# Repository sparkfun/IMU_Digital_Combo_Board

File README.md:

IMU Digital Combo Board-6 Degrees of Freedom-ITG3200/ADXL345
====================================================================
[
*IMU Digital Combo (SEN-10121)*](https://www.sparkfun.com/products/10121)

A simple breakout for the ADXL345 accelerometer and the ITG-3200 MEMS gyro. This board communicates over I2C. 

Repository Contents
-------------------
* **/Hardware** - All Eagle design files (.brd, .sch)
* **/Libraries** - All Arduino libraries and board examples
* **/Production** - Test bed files and production panel files

License Information
-------------------
The hardware is released under [Creative Commons ShareAlike 4.0 International](https://creativecommons.org/licenses/by-sa/4.0/).
The code is beerware; if you see me (or any other SparkFun employee) at the local, and you've found our code helpful, please buy us a round!

Distributed as-is; no warranty is given.

The original code library can be found [here](https://github.com/a1ronzo/6DOF-Digital).

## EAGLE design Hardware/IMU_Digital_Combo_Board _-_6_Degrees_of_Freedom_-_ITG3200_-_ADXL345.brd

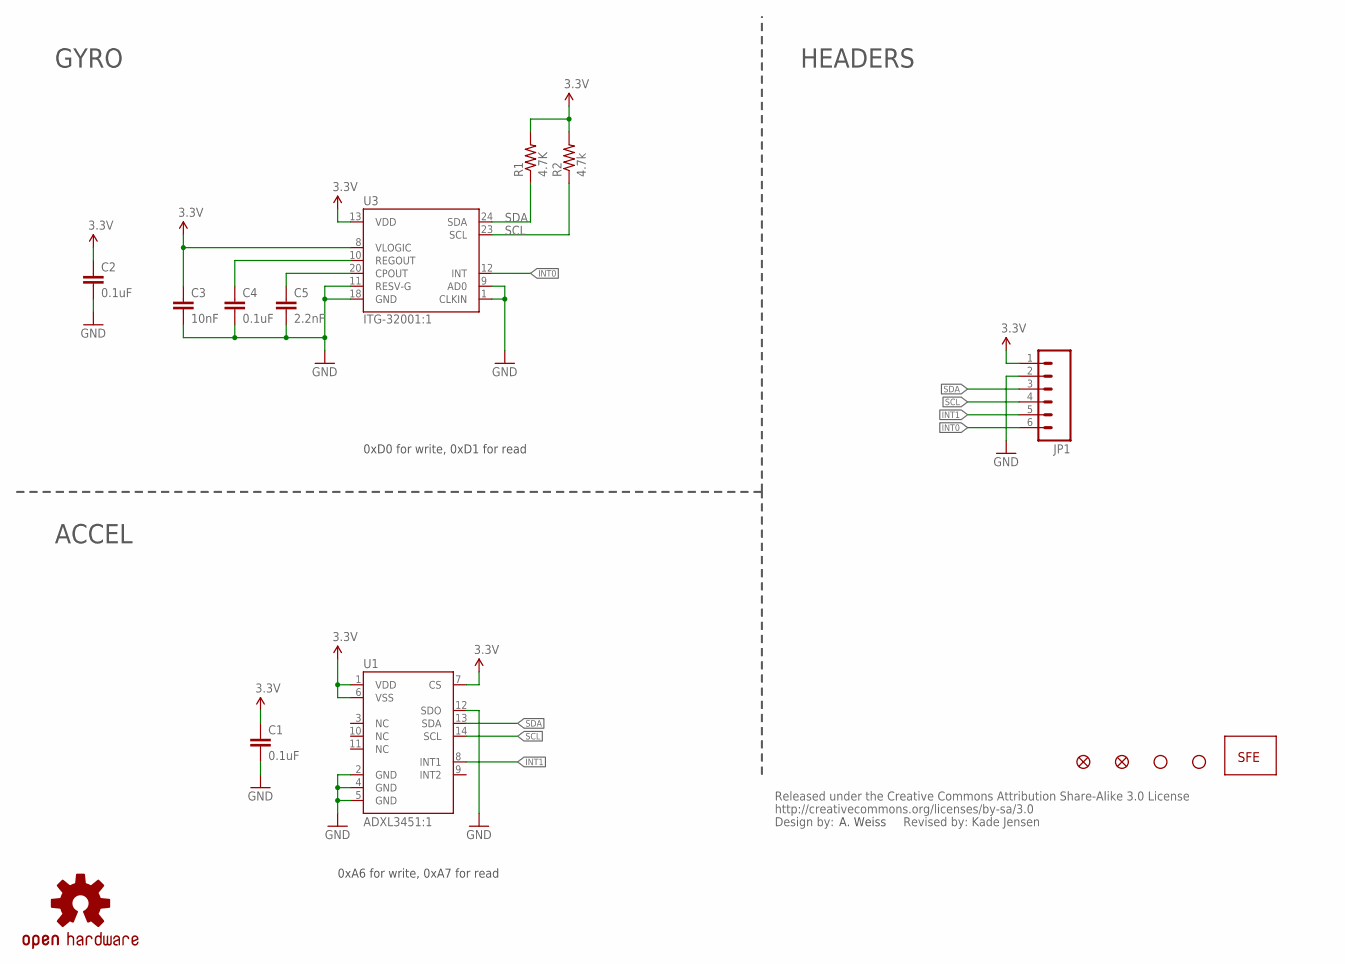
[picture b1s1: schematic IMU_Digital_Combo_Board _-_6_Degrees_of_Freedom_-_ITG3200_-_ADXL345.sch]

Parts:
C1, C2, C4: 0.1uF; 0603-CAP
C3: 10nF; 0603-CAP
C5: 2.2nF; 0603-CAP
JP1: M06SIP; 1X06
JP2, JP5: STAND-OFF
JP3: LOGO-SFESK; SFE-LOGO-FLAME
JP4, JP6: FIDUCIAL1X2; FIDUCIAL-1X2
R1: 4.7K; 0603-RES
R2: 4.7k; 0603-RES
U1: ADXL3451:1; LGA14
U3: ITG-32001:1; QFN-24_ITG3200_1:1
U$1: CREATIVE_COMMONS
U$2: OSHW-LOGOS; OSHW-LOGO-S

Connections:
3.3V: C1.1, C2.1, C3.1, JP1.1, R1.2, R2.2, U1.1 (VDD), U1.6 (VSS), U1.7 (CS), U3.8 (VLOGIC), U3.13 (VDD)
GND: C1.2, C2.2, C3.2, C4.2, C5.2, JP1.2, U1.2 (GND), U1.4 (GND), U1.5 (GND), U1.12 (SDO), U3.1 (CLKIN), U3.9 (AD0), U3.11 (RESV-G), U3.18 (GND)
INT0: JP1.6, U3.12 (INT)
INT1: JP1.5, U1.8 (INT1)
unnamed: C5.1, U3.20 (CPOUT)
unnamed: C4.1, U3.10 (REGOUT)
SCL: JP1.4, R2.1, U1.14 (SCL), U3.23 (SCL)
SDA: JP1.3, R1.1, U1.13 (SDA), U3.24 (SDA)

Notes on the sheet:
A. Weiss
GYRO
ACCEL
HEADERS
0xD0 for write, 0xD1 for read
0xA6 for write, 0xA7 for read
Revised by: Kade Jensen

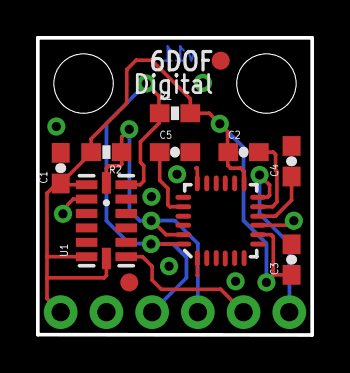
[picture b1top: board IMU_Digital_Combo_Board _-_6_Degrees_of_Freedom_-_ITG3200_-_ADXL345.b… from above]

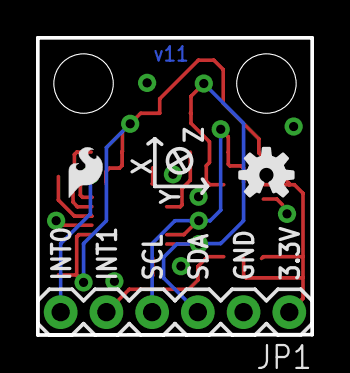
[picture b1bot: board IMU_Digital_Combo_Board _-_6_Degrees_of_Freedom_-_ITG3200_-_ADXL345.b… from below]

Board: 2 copper layers, 15.2 x 16.5 mm, 17 parts (3 on the bottom side), 8 nets.

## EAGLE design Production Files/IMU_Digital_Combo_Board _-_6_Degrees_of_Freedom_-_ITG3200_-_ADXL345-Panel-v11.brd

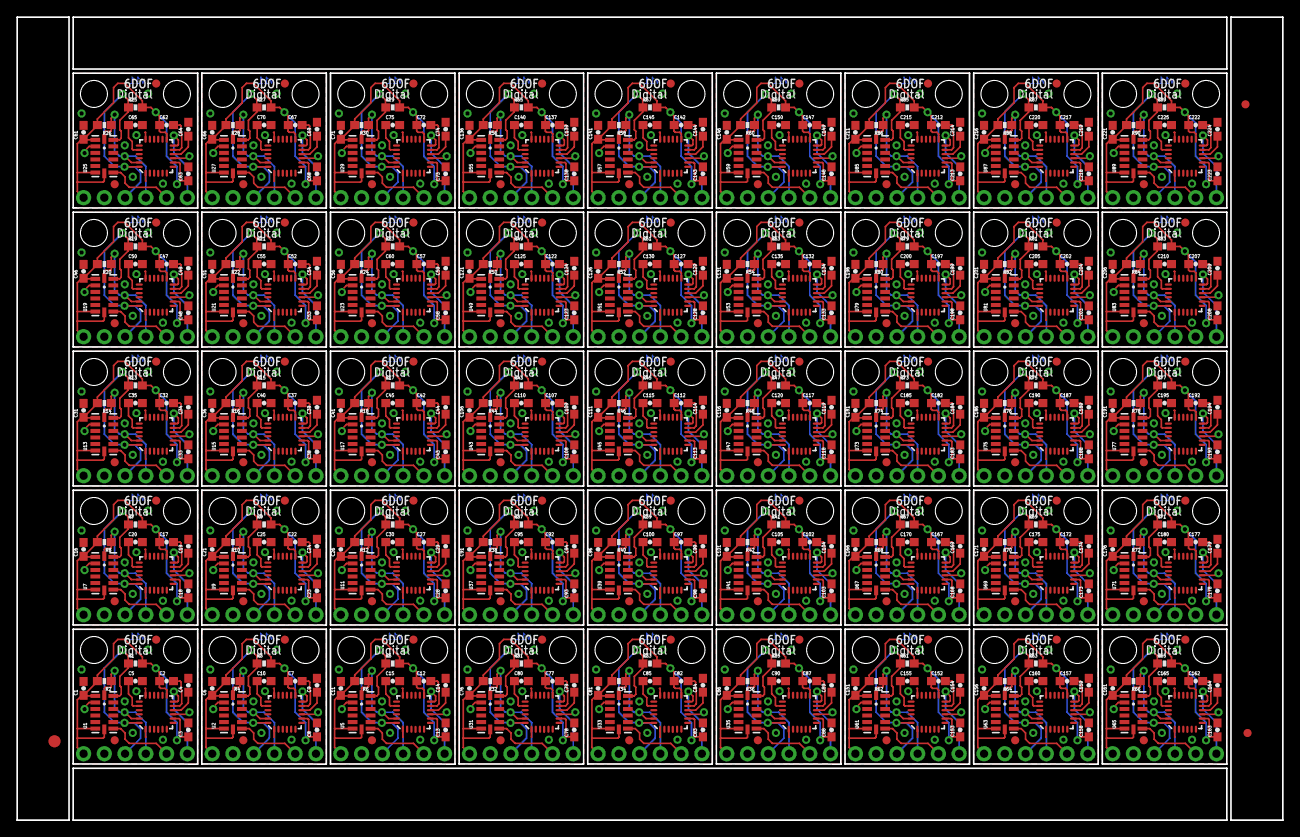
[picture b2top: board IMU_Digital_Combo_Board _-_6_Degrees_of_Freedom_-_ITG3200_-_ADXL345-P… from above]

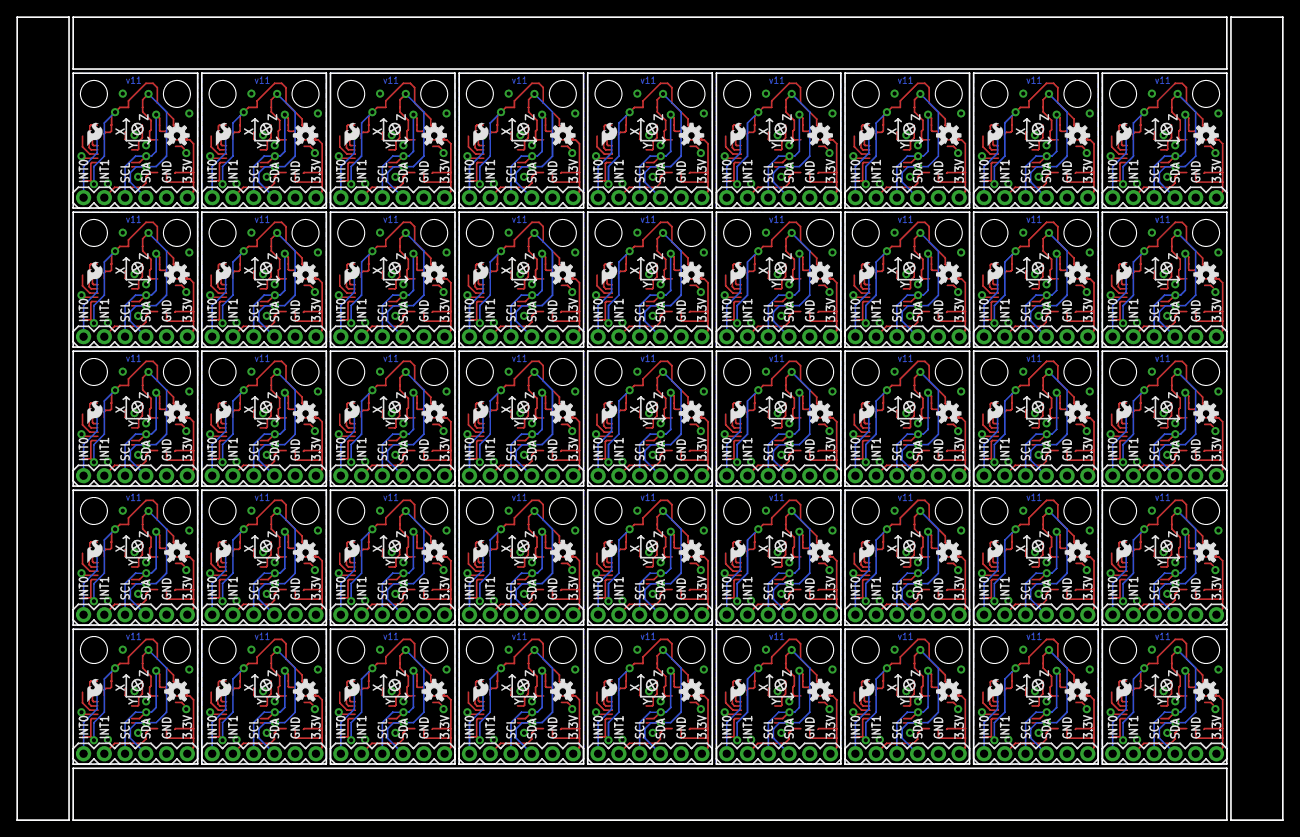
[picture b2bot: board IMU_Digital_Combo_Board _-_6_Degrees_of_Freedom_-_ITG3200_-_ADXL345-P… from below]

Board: 2 copper layers, 154.9 x 98.3 mm, 723 parts (135 on the bottom side), 360 nets.

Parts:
C1, C2, C4, C6, C7, C9, C11, C12, C14, C16, C17, C19, C21, C22, C24, C26, C27, C29, C31, C32, C34, C36, C37, C39, C41, C42, C44, C46, C47, C49, C51, C52, C54, C56, C57, C59, C61, C62, C64, C66, C67, C69, C71, C72, C74, C76, C77, C79, C81, C82, C84, C86, C87, C89, C91, C92, C94, C96, C97, C99, C101, C102, C104, C106, C107, C109, C111, C112, C114, C116, C117, C119, C121, C122, C124, C126, C127, C129, C131, C132, C134, C136, C137, C139, C141, C142, C144, C146, C147, C149, C151, C152, C154, C156, C157, C159, C161, C162, C164, C166, C167, C169, C171, C172, C174, C176, C177, C179, C181, C182, C184, C186, C187, C189, C191, C192, C194, C196, C197, C199, C201, C202, C204, C206, C207, C209, C211, C212, C214, C216, C217, C219, C221, C222, C224: 0.1uF; 0603-CAP
C3, C8, C13, C18, C23, C28, C33, C38, C43, C48, C53, C58, C63, C68, C73, C78, C83, C88, C93, C98, C103, C108, C113, C118, C123, C128, C133, C138, C143, C148, C153, C158, C163, C168, C173, C178, C183, C188, C193, C198, C203, C208, C213, C218, C223: 10nF; 0603-CAP
C5, C10, C15, C20, C25, C30, C35, C40, C45, C50, C55, C60, C65, C70, C75, C80, C85, C90, C95, C100, C105, C110, C115, C120, C125, C130, C135, C140, C145, C150, C155, C160, C165, C170, C175, C180, C185, C190, C195, C200, C205, C210, C215, C220, C225: 2.2nF; 0603-CAP
E$1: FIDUCIAL-1.5X3
E$4, E$6: FIDUCIAL-1X2
JP1, JP8, JP14, JP20, JP26, JP32, JP38, JP44, JP50, JP56, JP62, JP68, JP74, JP80, JP86, JP92, JP98, JP104, JP110, JP116, JP122, JP128, JP134, JP140, JP146, JP152, JP158, JP164, JP170, JP176, JP182, JP188, JP194, JP200, JP206, JP212, JP218, JP224, JP230, JP236, JP242, JP248, JP254, JP260, JP266: 1X06
JP2, JP5, JP9, JP10, JP15, JP16, JP21, JP22, JP27, JP28, JP33, JP34, JP39, JP40, JP45, JP46, JP51, JP52, JP57, JP58, JP63, JP64, JP69, JP70, JP75, JP76, JP81, JP82, JP87, JP88, JP93, JP94, JP99, JP100, JP105, JP106, JP111, JP112, JP117, JP118, JP123, JP124, JP129, JP130, JP135, JP136, JP141, JP142, JP147, JP148, JP153, JP154, JP159, JP160, JP165, JP166, JP171, JP172, JP177, JP178, JP183, JP184, JP189, JP190, JP195, JP196, JP201, JP202, JP207, JP208, JP213, JP214, JP219, JP220, JP225, JP226, JP231, JP232, JP237, JP238, JP243, JP244, JP249, JP250, JP255, JP256, JP261, JP262, JP267, JP268: STAND-OFF
JP3, JP7, JP13, JP19, JP25, JP31, JP37, JP43, JP49, JP55, JP61, JP67, JP73, JP79, JP85, JP91, JP97, JP103, JP109, JP115, JP121, JP127, JP133, JP139, JP145, JP151, JP157, JP163, JP169, JP175, JP181, JP187, JP193, JP199, JP205, JP211, JP217, JP223, JP229, JP235, JP241, JP247, JP253, JP259, JP265: LOGO-SFESK; SFE-LOGO-FLAME
JP4, JP6, JP11, JP12, JP17, JP18, JP23, JP24, JP29, JP30, JP35, JP36, JP41, JP42, JP47, JP48, JP53, JP54, JP59, JP60, JP65, JP66, JP71, JP72, JP77, JP78, JP83, JP84, JP89, JP90, JP95, JP96, JP101, JP102, JP107, JP108, JP113, JP114, JP119, JP120, JP125, JP126, JP131, JP132, JP137, JP138, JP143, JP144, JP149, JP150, JP155, JP156, JP161, JP162, JP167, JP168, JP173, JP174, JP179, JP180, JP185, JP186, JP191, JP192, JP197, JP198, JP203, JP204, JP209, JP210, JP215, JP216, JP221, JP222, JP227, JP228, JP233, JP234, JP239, JP240, JP245, JP246, JP251, JP252, JP257, JP258, JP263, JP264, JP269, JP270: FIDUCIAL1X2; FIDUCIAL-1X2
R1, R3, R5, R7, R9, R11, R13, R15, R17, R19, R21, R23, R25, R27, R29, R31, R33, R35, R37, R39, R41, R43, R45, R47, R49, R51, R53, R55, R57, R59, R61, R63, R65, R67, R69, R71, R73, R75, R77, R79, R81, R83, R85, R87, R89: 4.7K; 0603-RES
R2, R4, R6, R8, R10, R12, R14, R16, R18, R20, R22, R24, R26, R28, R30, R32, R34, R36, R38, R40, R42, R44, R46, R48, R50, R52, R54, R56, R58, R60, R62, R64, R66, R68, R70, R72, R74, R76, R78, R80, R82, R84, R86, R88, R90: 4.7k; 0603-RES
U1, U2, U5, U7, U9, U11, U13, U15, U17, U19, U21, U23, U25, U27, U29, U31, U33, U35, U37, U39, U41, U43, U45, U47, U49, U51, U53, U55, U57, U59, U61, U63, U65, U67, U69, U71, U73, U75, U77, U79, U81, U83, U85, U87, U89: ADXL3451:1; LGA14
U3, U4, U6, U8, U10, U12, U14, U16, U18, U20, U22, U24, U26, U28, U30, U32, U34, U36, U38, U40, U42, U44, U46, U48, U50, U52, U54, U56, U58, U60, U62, U64, U66, U68, U70, U72, U74, U76, U78, U80, U82, U84, U86, U88, U90: ITG-32001:1; QFN-24_ITG3200_1:1
U$1, U$2, U$3, U$4, U$5, U$6, U$7, U$8, U$9, U$10, U$11, U$12, U$13, U$14, U$15, U$16, U$17, U$18, U$19, U$20, U$21, U$22, U$23, U$24, U$25, U$26, U$27, U$28, U$29, U$30, U$31, U$32, U$33, U$34, U$35, U$36, U$37, U$38, U$39, U$40, U$41, U$42, U$43, U$44, U$45: OSHW-LOGOS; OSHW-LOGO-S

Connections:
3.3V: C1.1, C2.1, C3.1, JP1.1, R1.2, R2.2, U1.1, U1.6, U1.7, U3.8, U3.13
3.3V1: C6.1, C7.1, C8.1, JP8.1, R3.2, R4.2, U2.1, U2.6, U2.7, U4.8, U4.13
3.3V2: C11.1, C12.1, C13.1, JP14.1, R5.2, R6.2, U5.1, U5.6, U5.7, U6.8, U6.13
3.3V3: C16.1, C17.1, C18.1, JP20.1, R7.2, R8.2, U7.1, U7.6, U7.7, U8.8, U8.13
3.3V4: C21.1, C22.1, C23.1, JP26.1, R9.2, R10.2, U9.1, U9.6, U9.7, U10.8, U10.13
3.3V5: C26.1, C27.1, C28.1, JP32.1, R11.2, R12.2, U11.1, U11.6, U11.7, U12.8, U12.13
3.3V6: C31.1, C32.1, C33.1, JP38.1, R13.2, R14.2, U13.1, U13.6, U13.7, U14.8, U14.13
3.3V7: C36.1, C37.1, C38.1, JP44.1, R15.2, R16.2, U15.1, U15.6, U15.7, U16.8, U16.13
3.3V8: C41.1, C42.1, C43.1, JP50.1, R17.2, R18.2, U17.1, U17.6, U17.7, U18.8, U18.13
3.3V9: C46.1, C47.1, C48.1, JP56.1, R19.2, R20.2, U19.1, U19.6, U19.7, U20.8, U20.13
3.3V10: C51.1, C52.1, C53.1, JP62.1, R21.2, R22.2, U21.1, U21.6, U21.7, U22.8, U22.13
3.3V11: C56.1, C57.1, C58.1, JP68.1, R23.2, R24.2, U23.1, U23.6, U23.7, U24.8, U24.13
3.3V12: C61.1, C62.1, C63.1, JP74.1, R25.2, R26.2, U25.1, U25.6, U25.7, U26.8, U26.13
3.3V13: C66.1, C67.1, C68.1, JP80.1, R27.2, R28.2, U27.1, U27.6, U27.7, U28.8, U28.13
3.3V14: C71.1, C72.1, C73.1, JP86.1, R29.2, R30.2, U29.1, U29.6, U29.7, U30.8, U30.13
3.3V15: C76.1, C77.1, C78.1, JP92.1, R31.2, R32.2, U31.1, U31.6, U31.7, U32.8, U32.13
3.3V16: C81.1, C82.1, C83.1, JP98.1, R33.2, R34.2, U33.1, U33.6, U33.7, U34.8, U34.13
3.3V17: C86.1, C87.1, C88.1, JP104.1, R35.2, R36.2, U35.1, U35.6, U35.7, U36.8, U36.13
3.3V18: C91.1, C92.1, C93.1, JP110.1, R37.2, R38.2, U37.1, U37.6, U37.7, U38.8, U38.13
3.3V19: C96.1, C97.1, C98.1, JP116.1, R39.2, R40.2, U39.1, U39.6, U39.7, U40.8, U40.13
3.3V20: C101.1, C102.1, C103.1, JP122.1, R41.2, R42.2, U41.1, U41.6, U41.7, U42.8, U42.13
3.3V21: C106.1, C107.1, C108.1, JP128.1, R43.2, R44.2, U43.1, U43.6, U43.7, U44.8, U44.13
3.3V22: C111.1, C112.1, C113.1, JP134.1, R45.2, R46.2, U45.1, U45.6, U45.7, U46.8, U46.13
3.3V23: C116.1, C117.1, C118.1, JP140.1, R47.2, R48.2, U47.1, U47.6, U47.7, U48.8, U48.13
3.3V24: C121.1, C122.1, C123.1, JP146.1, R49.2, R50.2, U49.1, U49.6, U49.7, U50.8, U50.13
3.3V25: C126.1, C127.1, C128.1, JP152.1, R51.2, R52.2, U51.1, U51.6, U51.7, U52.8, U52.13
3.3V26: C131.1, C132.1, C133.1, JP158.1, R53.2, R54.2, U53.1, U53.6, U53.7, U54.8, U54.13
3.3V27: C136.1, C137.1, C138.1, JP164.1, R55.2, R56.2, U55.1, U55.6, U55.7, U56.8, U56.13
3.3V28: C141.1, C142.1, C143.1, JP170.1, R57.2, R58.2, U57.1, U57.6, U57.7, U58.8, U58.13
3.3V29: C146.1, C147.1, C148.1, JP176.1, R59.2, R60.2, U59.1, U59.6, U59.7, U60.8, U60.13
3.3V30: C151.1, C152.1, C153.1, JP182.1, R61.2, R62.2, U61.1, U61.6, U61.7, U62.8, U62.13
3.3V31: C156.1, C157.1, C158.1, JP188.1, R63.2, R64.2, U63.1, U63.6, U63.7, U64.8, U64.13
3.3V32: C161.1, C162.1, C163.1, JP194.1, R65.2, R66.2, U65.1, U65.6, U65.7, U66.8, U66.13
3.3V33: C166.1, C167.1, C168.1, JP200.1, R67.2, R68.2, U67.1, U67.6, U67.7, U68.8, U68.13
3.3V34: C171.1, C172.1, C173.1, JP206.1, R69.2, R70.2, U69.1, U69.6, U69.7, U70.8, U70.13
3.3V35: C176.1, C177.1, C178.1, JP212.1, R71.2, R72.2, U71.1, U71.6, U71.7, U72.8, U72.13
3.3V36: C181.1, C182.1, C183.1, JP218.1, R73.2, R74.2, U73.1, U73.6, U73.7, U74.8, U74.13
3.3V37: C186.1, C187.1, C188.1, JP224.1, R75.2, R76.2, U75.1, U75.6, U75.7, U76.8, U76.13
3.3V38: C191.1, C192.1, C193.1, JP230.1, R77.2, R78.2, U77.1, U77.6, U77.7, U78.8, U78.13
3.3V39: C196.1, C197.1, C198.1, JP236.1, R79.2, R80.2, U79.1, U79.6, U79.7, U80.8, U80.13
3.3V40: C201.1, C202.1, C203.1, JP242.1, R81.2, R82.2, U81.1, U81.6, U81.7, U82.8, U82.13
3.3V41: C206.1, C207.1, C208.1, JP248.1, R83.2, R84.2, U83.1, U83.6, U83.7, U84.8, U84.13
3.3V42: C211.1, C212.1, C213.1, JP254.1, R85.2, R86.2, U85.1, U85.6, U85.7, U86.8, U86.13
3.3V43: C216.1, C217.1, C218.1, JP260.1, R87.2, R88.2, U87.1, U87.6, U87.7, U88.8, U88.13
3.3V44: C221.1, C222.1, C223.1, JP266.1, R89.2, R90.2, U89.1, U89.6, U89.7, U90.8, U90.13
GND: C1.2, C2.2, C3.2, C4.2, C5.2, JP1.2, U1.2, U1.4, U1.5, U1.12, U3.1, U3.9, U3.11, U3.18
GND1: C6.2, C7.2, C8.2, C9.2, C10.2, JP8.2, U2.2, U2.4, U2.5, U2.12, U4.1, U4.9, U4.11, U4.18
GND2: C11.2, C12.2, C13.2, C14.2, C15.2, JP14.2, U5.2, U5.4, U5.5, U5.12, U6.1, U6.9, U6.11, U6.18
GND3: C16.2, C17.2, C18.2, C19.2, C20.2, JP20.2, U7.2, U7.4, U7.5, U7.12, U8.1, U8.9, U8.11, U8.18
GND4: C21.2, C22.2, C23.2, C24.2, C25.2, JP26.2, U9.2, U9.4, U9.5, U9.12, U10.1, U10.9, U10.11, U10.18
GND5: C26.2, C27.2, C28.2, C29.2, C30.2, JP32.2, U11.2, U11.4, U11.5, U11.12, U12.1, U12.9, U12.11, U12.18
GND6: C31.2, C32.2, C33.2, C34.2, C35.2, JP38.2, U13.2, U13.4, U13.5, U13.12, U14.1, U14.9, U14.11, U14.18
GND7: C36.2, C37.2, C38.2, C39.2, C40.2, JP44.2, U15.2, U15.4, U15.5, U15.12, U16.1, U16.9, U16.11, U16.18
GND8: C41.2, C42.2, C43.2, C44.2, C45.2, JP50.2, U17.2, U17.4, U17.5, U17.12, U18.1, U18.9, U18.11, U18.18
GND9: C46.2, C47.2, C48.2, C49.2, C50.2, JP56.2, U19.2, U19.4, U19.5, U19.12, U20.1, U20.9, U20.11, U20.18
GND10: C51.2, C52.2, C53.2, C54.2, C55.2, JP62.2, U21.2, U21.4, U21.5, U21.12, U22.1, U22.9, U22.11, U22.18
GND11: C56.2, C57.2, C58.2, C59.2, C60.2, JP68.2, U23.2, U23.4, U23.5, U23.12, U24.1, U24.9, U24.11, U24.18
GND12: C61.2, C62.2, C63.2, C64.2, C65.2, JP74.2, U25.2, U25.4, U25.5, U25.12, U26.1, U26.9, U26.11, U26.18
GND13: C66.2, C67.2, C68.2, C69.2, C70.2, JP80.2, U27.2, U27.4, U27.5, U27.12, U28.1, U28.9, U28.11, U28.18
GND14: C71.2, C72.2, C73.2, C74.2, C75.2, JP86.2, U29.2, U29.4, U29.5, U29.12, U30.1, U30.9, U30.11, U30.18
GND15: C76.2, C77.2, C78.2, C79.2, C80.2, JP92.2, U31.2, U31.4, U31.5, U31.12, U32.1, U32.9, U32.11, U32.18
GND16: C81.2, C82.2, C83.2, C84.2, C85.2, JP98.2, U33.2, U33.4, U33.5, U33.12, U34.1, U34.9, U34.11, U34.18
GND17: C86.2, C87.2, C88.2, C89.2, C90.2, JP104.2, U35.2, U35.4, U35.5, U35.12, U36.1, U36.9, U36.11, U36.18
GND18: C91.2, C92.2, C93.2, C94.2, C95.2, JP110.2, U37.2, U37.4, U37.5, U37.12, U38.1, U38.9, U38.11, U38.18
GND19: C96.2, C97.2, C98.2, C99.2, C100.2, JP116.2, U39.2, U39.4, U39.5, U39.12, U40.1, U40.9, U40.11, U40.18
GND20: C101.2, C102.2, C103.2, C104.2, C105.2, JP122.2, U41.2, U41.4, U41.5, U41.12, U42.1, U42.9, U42.11, U42.18
GND21: C106.2, C107.2, C108.2, C109.2, C110.2, JP128.2, U43.2, U43.4, U43.5, U43.12, U44.1, U44.9, U44.11, U44.18
GND22: C111.2, C112.2, C113.2, C114.2, C115.2, JP134.2, U45.2, U45.4, U45.5, U45.12, U46.1, U46.9, U46.11, U46.18
GND23: C116.2, C117.2, C118.2, C119.2, C120.2, JP140.2, U47.2, U47.4, U47.5, U47.12, U48.1, U48.9, U48.11, U48.18
GND24: C121.2, C122.2, C123.2, C124.2, C125.2, JP146.2, U49.2, U49.4, U49.5, U49.12, U50.1, U50.9, U50.11, U50.18
GND25: C126.2, C127.2, C128.2, C129.2, C130.2, JP152.2, U51.2, U51.4, U51.5, U51.12, U52.1, U52.9, U52.11, U52.18
GND26: C131.2, C132.2, C133.2, C134.2, C135.2, JP158.2, U53.2, U53.4, U53.5, U53.12, U54.1, U54.9, U54.11, U54.18
GND27: C136.2, C137.2, C138.2, C139.2, C140.2, JP164.2, U55.2, U55.4, U55.5, U55.12, U56.1, U56.9, U56.11, U56.18
GND28: C141.2, C142.2, C143.2, C144.2, C145.2, JP170.2, U57.2, U57.4, U57.5, U57.12, U58.1, U58.9, U58.11, U58.18
GND29: C146.2, C147.2, C148.2, C149.2, C150.2, JP176.2, U59.2, U59.4, U59.5, U59.12, U60.1, U60.9, U60.11, U60.18
GND30: C151.2, C152.2, C153.2, C154.2, C155.2, JP182.2, U61.2, U61.4, U61.5, U61.12, U62.1, U62.9, U62.11, U62.18
GND31: C156.2, C157.2, C158.2, C159.2, C160.2, JP188.2, U63.2, U63.4, U63.5, U63.12, U64.1, U64.9, U64.11, U64.18
GND32: C161.2, C162.2, C163.2, C164.2, C165.2, JP194.2, U65.2, U65.4, U65.5, U65.12, U66.1, U66.9, U66.11, U66.18
GND33: C166.2, C167.2, C168.2, C169.2, C170.2, JP200.2, U67.2, U67.4, U67.5, U67.12, U68.1, U68.9, U68.11, U68.18
GND34: C171.2, C172.2, C173.2, C174.2, C175.2, JP206.2, U69.2, U69.4, U69.5, U69.12, U70.1, U70.9, U70.11, U70.18
GND35: C176.2, C177.2, C178.2, C179.2, C180.2, JP212.2, U71.2, U71.4, U71.5, U71.12, U72.1, U72.9, U72.11, U72.18
GND36: C181.2, C182.2, C183.2, C184.2, C185.2, JP218.2, U73.2, U73.4, U73.5, U73.12, U74.1, U74.9, U74.11, U74.18
GND37: C186.2, C187.2, C188.2, C189.2, C190.2, JP224.2, U75.2, U75.4, U75.5, U75.12, U76.1, U76.9, U76.11, U76.18
GND38: C191.2, C192.2, C193.2, C194.2, C195.2, JP230.2, U77.2, U77.4, U77.5, U77.12, U78.1, U78.9, U78.11, U78.18
GND39: C196.2, C197.2, C198.2, C199.2, C200.2, JP236.2, U79.2, U79.4, U79.5, U79.12, U80.1, U80.9, U80.11, U80.18
GND40: C201.2, C202.2, C203.2, C204.2, C205.2, JP242.2, U81.2, U81.4, U81.5, U81.12, U82.1, U82.9, U82.11, U82.18
GND41: C206.2, C207.2, C208.2, C209.2, C210.2, JP248.2, U83.2, U83.4, U83.5, U83.12, U84.1, U84.9, U84.11, U84.18
GND42: C211.2, C212.2, C213.2, C214.2, C215.2, JP254.2, U85.2, U85.4, U85.5, U85.12, U86.1, U86.9, U86.11, U86.18
GND43: C216.2, C217.2, C218.2, C219.2, C220.2, JP260.2, U87.2, U87.4, U87.5, U87.12, U88.1, U88.9, U88.11, U88.18
GND44: C221.2, C222.2, C223.2, C224.2, C225.2, JP266.2, U89.2, U89.4, U89.5, U89.12, U90.1, U90.9, U90.11, U90.18
INT0: JP1.6, U3.12
INT1: JP1.5, U1.8
INT2: JP8.5, U2.8
INT3: JP8.6, U4.12
INT4: JP14.5, U5.8
INT5: JP14.6, U6.12
INT6: JP20.5, U7.8
INT7: JP20.6, U8.12
INT8: JP26.5, U9.8
INT9: JP26.6, U10.12
INT10: JP32.5, U11.8
INT11: JP32.6, U12.12
INT12: JP38.5, U13.8
INT13: JP38.6, U14.12
INT14: JP44.5, U15.8
INT15: JP44.6, U16.12
INT16: JP50.5, U17.8
INT17: JP50.6, U18.12
INT18: JP56.5, U19.8
INT19: JP56.6, U20.12
INT20: JP62.5, U21.8
INT21: JP62.6, U22.12
INT22: JP68.5, U23.8
INT23: JP68.6, U24.12
INT24: JP74.5, U25.8
INT25: JP74.6, U26.12
INT26: JP80.5, U27.8
INT27: JP80.6, U28.12
INT28: JP86.5, U29.8
INT29: JP86.6, U30.12
INT30: JP92.5, U31.8
INT31: JP92.6, U32.12
INT32: JP98.5, U33.8
INT33: JP98.6, U34.12
INT34: JP104.5, U35.8
INT35: JP104.6, U36.12
INT36: JP110.5, U37.8
INT37: JP110.6, U38.12
INT38: JP116.5, U39.8
INT39: JP116.6, U40.12
INT40: JP122.5, U41.8
INT41: JP122.6, U42.12
INT42: JP128.5, U43.8
INT43: JP128.6, U44.12
INT44: JP134.5, U45.8
INT45: JP134.6, U46.12
INT46: JP140.5, U47.8
INT47: JP140.6, U48.12
INT48: JP146.5, U49.8
INT49: JP146.6, U50.12
INT50: JP152.5, U51.8
INT51: JP152.6, U52.12
INT52: JP158.5, U53.8
INT53: JP158.6, U54.12
INT54: JP164.5, U55.8
INT55: JP164.6, U56.12
INT56: JP170.5, U57.8
INT57: JP170.6, U58.12
INT58: JP176.5, U59.8
INT59: JP176.6, U60.12
INT60: JP182.5, U61.8
INT61: JP182.6, U62.12
INT62: JP188.5, U63.8
INT63: JP188.6, U64.12
INT64: JP194.5, U65.8
INT65: JP194.6, U66.12
INT66: JP200.5, U67.8
INT67: JP200.6, U68.12
INT68: JP206.5, U69.8
INT69: JP206.6, U70.12
INT70: JP212.5, U71.8
INT71: JP212.6, U72.12
INT72: JP218.5, U73.8
INT73: JP218.6, U74.12
INT74: JP224.5, U75.8
INT75: JP224.6, U76.12
INT76: JP230.5, U77.8
INT77: JP230.6, U78.12
INT78: JP236.5, U79.8
INT79: JP236.6, U80.12
INT80: JP242.5, U81.8
INT81: JP242.6, U82.12
INT82: JP248.5, U83.8
INT83: JP248.6, U84.12
INT84: JP254.5, U85.8
INT85: JP254.6, U86.12
INT86: JP260.5, U87.8
INT87: JP260.6, U88.12
INT88: JP266.5, U89.8
INT89: JP266.6, U90.12
unnamed: C10.1, U4.20
unnamed: C5.1, U3.20
unnamed: C4.1, U3.10
unnamed: C9.1, U4.10
unnamed: C15.1, U6.20
unnamed: C14.1, U6.10
unnamed: C20.1, U8.20
unnamed: C19.1, U8.10
unnamed: C25.1, U10.20
unnamed: C24.1, U10.10
unnamed: C30.1, U12.20
unnamed: C29.1, U12.10
unnamed: C35.1, U14.20
unnamed: C34.1, U14.10
unnamed: C40.1, U16.20
unnamed: C39.1, U16.10
unnamed: C45.1, U18.20
unnamed: C44.1, U18.10
unnamed: C50.1, U20.20
unnamed: C49.1, U20.10
unnamed: C55.1, U22.20
unnamed: C54.1, U22.10
unnamed: C60.1, U24.20
unnamed: C59.1, U24.10
unnamed: C65.1, U26.20
unnamed: C64.1, U26.10
unnamed: C70.1, U28.20
unnamed: C69.1, U28.10
unnamed: C75.1, U30.20
unnamed: C74.1, U30.10
unnamed: C80.1, U32.20
unnamed: C79.1, U32.10
unnamed: C85.1, U34.20
unnamed: C84.1, U34.10
unnamed: C90.1, U36.20
unnamed: C89.1, U36.10
unnamed: C95.1, U38.20
unnamed: C94.1, U38.10
unnamed: C100.1, U40.20
unnamed: C99.1, U40.10
unnamed: C105.1, U42.20
unnamed: C104.1, U42.10
unnamed: C110.1, U44.20
unnamed: C109.1, U44.10
unnamed: C115.1, U46.20
unnamed: C114.1, U46.10
unnamed: C120.1, U48.20
unnamed: C119.1, U48.10
unnamed: C125.1, U50.20
unnamed: C124.1, U50.10
unnamed: C130.1, U52.20
unnamed: C129.1, U52.10
unnamed: C135.1, U54.20
unnamed: C134.1, U54.10
unnamed: C140.1, U56.20
unnamed: C139.1, U56.10
unnamed: C145.1, U58.20
unnamed: C144.1, U58.10
unnamed: C150.1, U60.20
unnamed: C149.1, U60.10
unnamed: C155.1, U62.20
unnamed: C154.1, U62.10
unnamed: C160.1, U64.20
unnamed: C159.1, U64.10
unnamed: C165.1, U66.20
unnamed: C164.1, U66.10
unnamed: C170.1, U68.20
unnamed: C169.1, U68.10
unnamed: C175.1, U70.20
unnamed: C174.1, U70.10
unnamed: C180.1, U72.20
unnamed: C179.1, U72.10
unnamed: C185.1, U74.20
unnamed: C184.1, U74.10
unnamed: C190.1, U76.20
unnamed: C189.1, U76.10
unnamed: C195.1, U78.20
unnamed: C194.1, U78.10
unnamed: C200.1, U80.20
unnamed: C199.1, U80.10
unnamed: C205.1, U82.20
unnamed: C204.1, U82.10
unnamed: C210.1, U84.20
unnamed: C209.1, U84.10
unnamed: C215.1, U86.20
unnamed: C214.1, U86.10
unnamed: C220.1, U88.20
unnamed: C219.1, U88.10
unnamed: C225.1, U90.20
unnamed: C224.1, U90.10
SCL: JP1.4, R2.1, U1.14, U3.23
SCL1: JP8.4, R4.1, U2.14, U4.23
SCL2: JP14.4, R6.1, U5.14, U6.23
SCL3: JP20.4, R8.1, U7.14, U8.23
SCL4: JP26.4, R10.1, U9.14, U10.23
SCL5: JP32.4, R12.1, U11.14, U12.23
SCL6: JP38.4, R14.1, U13.14, U14.23
SCL7: JP44.4, R16.1, U15.14, U16.23
SCL8: JP50.4, R18.1, U17.14, U18.23
SCL9: JP56.4, R20.1, U19.14, U20.23
SCL10: JP62.4, R22.1, U21.14, U22.23
SCL11: JP68.4, R24.1, U23.14, U24.23
SCL12: JP74.4, R26.1, U25.14, U26.23
SCL13: JP80.4, R28.1, U27.14, U28.23
SCL14: JP86.4, R30.1, U29.14, U30.23
SCL15: JP92.4, R32.1, U31.14, U32.23
SCL16: JP98.4, R34.1, U33.14, U34.23
SCL17: JP104.4, R36.1, U35.14, U36.23
SCL18: JP110.4, R38.1, U37.14, U38.23
SCL19: JP116.4, R40.1, U39.14, U40.23
SCL20: JP122.4, R42.1, U41.14, U42.23
SCL21: JP128.4, R44.1, U43.14, U44.23
SCL22: JP134.4, R46.1, U45.14, U46.23
SCL23: JP140.4, R48.1, U47.14, U48.23
SCL24: JP146.4, R50.1, U49.14, U50.23
SCL25: JP152.4, R52.1, U51.14, U52.23
SCL26: JP158.4, R54.1, U53.14, U54.23
SCL27: JP164.4, R56.1, U55.14, U56.23
SCL28: JP170.4, R58.1, U57.14, U58.23
SCL29: JP176.4, R60.1, U59.14, U60.23
SCL30: JP182.4, R62.1, U61.14, U62.23
SCL31: JP188.4, R64.1, U63.14, U64.23
SCL32: JP194.4, R66.1, U65.14, U66.23
SCL33: JP200.4, R68.1, U67.14, U68.23
SCL34: JP206.4, R70.1, U69.14, U70.23
SCL35: JP212.4, R72.1, U71.14, U72.23
SCL36: JP218.4, R74.1, U73.14, U74.23
SCL37: JP224.4, R76.1, U75.14, U76.23
SCL38: JP230.4, R78.1, U77.14, U78.23
SCL39: JP236.4, R80.1, U79.14, U80.23
SCL40: JP242.4, R82.1, U81.14, U82.23
SCL41: JP248.4, R84.1, U83.14, U84.23
SCL42: JP254.4, R86.1, U85.14, U86.23
SCL43: JP260.4, R88.1, U87.14, U88.23
SCL44: JP266.4, R90.1, U89.14, U90.23
SDA: JP1.3, R1.1, U1.13, U3.24
SDA1: JP8.3, R3.1, U2.13, U4.24
SDA2: JP14.3, R5.1, U5.13, U6.24
SDA3: JP20.3, R7.1, U7.13, U8.24
SDA4: JP26.3, R9.1, U9.13, U10.24
SDA5: JP32.3, R11.1, U11.13, U12.24
SDA6: JP38.3, R13.1, U13.13, U14.24
SDA7: JP44.3, R15.1, U15.13, U16.24
SDA8: JP50.3, R17.1, U17.13, U18.24
SDA9: JP56.3, R19.1, U19.13, U20.24
SDA10: JP62.3, R21.1, U21.13, U22.24
SDA11: JP68.3, R23.1, U23.13, U24.24
SDA12: JP74.3, R25.1, U25.13, U26.24
SDA13: JP80.3, R27.1, U27.13, U28.24
SDA14: JP86.3, R29.1, U29.13, U30.24
SDA15: JP92.3, R31.1, U31.13, U32.24
SDA16: JP98.3, R33.1, U33.13, U34.24
SDA17: JP104.3, R35.1, U35.13, U36.24
SDA18: JP110.3, R37.1, U37.13, U38.24
SDA19: JP116.3, R39.1, U39.13, U40.24
SDA20: JP122.3, R41.1, U41.13, U42.24
SDA21: JP128.3, R43.1, U43.13, U44.24
SDA22: JP134.3, R45.1, U45.13, U46.24
SDA23: JP140.3, R47.1, U47.13, U48.24
SDA24: JP146.3, R49.1, U49.13, U50.24
SDA25: JP152.3, R51.1, U51.13, U52.24
SDA26: JP158.3, R53.1, U53.13, U54.24
SDA27: JP164.3, R55.1, U55.13, U56.24
SDA28: JP170.3, R57.1, U57.13, U58.24
SDA29: JP176.3, R59.1, U59.13, U60.24
SDA30: JP182.3, R61.1, U61.13, U62.24
SDA31: JP188.3, R63.1, U63.13, U64.24
SDA32: JP194.3, R65.1, U65.13, U66.24
SDA33: JP200.3, R67.1, U67.13, U68.24
SDA34: JP206.3, R69.1, U69.13, U70.24
SDA35: JP212.3, R71.1, U71.13, U72.24
SDA36: JP218.3, R73.1, U73.13, U74.24
SDA37: JP224.3, R75.1, U75.13, U76.24
SDA38: JP230.3, R77.1, U77.13, U78.24
SDA39: JP236.3, R79.1, U79.13, U80.24
SDA40: JP242.3, R81.1, U81.13, U82.24
SDA41: JP248.3, R83.1, U83.13, U84.24
SDA42: JP254.3, R85.1, U85.13, U86.24
SDA43: JP260.3, R87.1, U87.13, U88.24
SDA44: JP266.3, R89.1, U89.13, U90.24

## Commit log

2013-07-10 Initial Commit of v11 of IMU 6DOF
    Initial commit of updated IMU 6DOF breakout, v11. Changes from v10:
    -Update ITG-3200 1:1 footprint
    -0402 to 0603 footprints for all caps and resistors
    -Added OSHW logo
    -Added version number
    -rerouted traces away from ITG-3200 IC
2013-07-11 Added production fiducials
    Added:
    - production fiducials
    - flags in schematic for net labels
    - modified two traces for better signal integrity
2013-07-12 Moved files to hardware folder
    Moved files to hardware folder to match standard organization.
2013-07-15 Proper CC 3.0 Attribution
    Added proper CC 3.0 attribution in board and schematic.
2013-08-12 Updated ADXL345 Package and connected SDA signal
    SDA trace had gotten dropped in previous design by accident. Reconnected
    now and took the opportunity to include new ADXL345 footprint. Had to
    change the route job significantly to make it all fit.
2013-08-14 Rerouted a few traces
    Changed two 3.3V and one of the INT traces for cleaner signal. Moved a
    GND via and a fiducial as well.
2013-08-15 Resyncing with Schematic
    Last commit didn't sync the .sch file. Weird.
2013-09-04 New Panel
    new panel that is 9x5, can be broken down into 3x5 for ganged testing
2013-09-05 deleted gerbers
2014-02-06 Updating README, cleaning up board files, adding library

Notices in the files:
parts and their libraries:
SparkFun: Released under the Creative Commons Attribution Share-Alike 3.0 License
SparkFun: http://creativecommons.org/licenses/by-sa/3.0
SparkFun-Aesthetics: Licensing: CC v3.0 Share-Alike You are welcome to use this library for commercial purposes.
